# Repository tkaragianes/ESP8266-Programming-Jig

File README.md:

Repo to store design files, schematics, circuit layout, code, etc for an ESP8266 programming jig. Designed to service the ESP-01, ESP-12, & ESP-201 modules.

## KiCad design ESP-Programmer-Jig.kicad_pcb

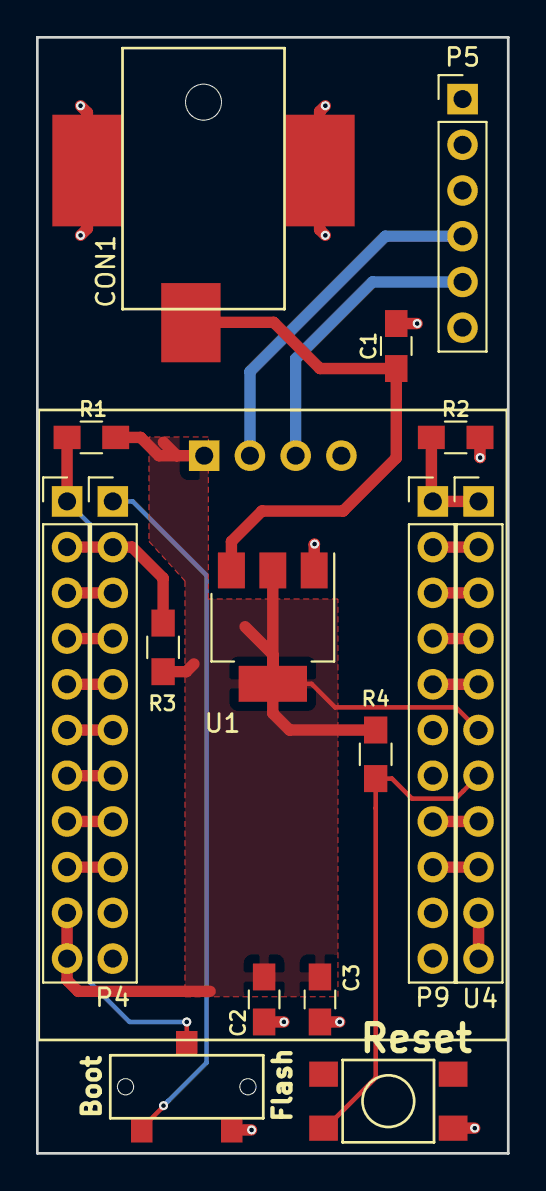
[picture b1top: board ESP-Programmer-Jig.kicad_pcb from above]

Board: 2 copper layers, 26.2 x 62.0 mm, 15 parts (0 on the bottom side), 23 nets.

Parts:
C1, C2: 10uF; C_0805_HandSoldering
C3: 0.1uF; C_0805_HandSoldering
CON1: BARREL_JACK; PJ-036AH-SMT_BarrelJack
P4, P9: CONN_01X11; Pin_Header_Straight_1x11_Pitch2.54mm
P5: CONN_01X06; Pin_Header_Straight_1x06_Pitch2.54mm
R1, R2, R3, R4: 10k; R_0805_HandSoldering
SW1: SW_PUSH; TL3305_Tact_Switch
SW2: SW_SPDT; Slide_Switch_SPDT
U1: AZ1117; SOT-223
U4: ESP-201; ESP-201_Socket

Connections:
+3V3: C2.1, C3.1, R1.1, R3.1, R4.1, U1.2, U1.4, U4.1, U4.14, U4.15, U4.21
CLK: P4.4, U4.8
CMD: P4.5, U4.9
D0: P4.6, U4.10
D1: P4.7, U4.11
D2: P4.3, U4.7
D3: P4.8, U4.12
Flash: R1.2, SW2.2, U4.5
GND: C1.2, C2.2, C3.2, CON1.2, CON1.3, P5.1, R2.1, SW1.2, SW2.3, U1.1, U4.4, U4.25, U4.26
IO0: P4.1, SW2.1
IO2: P4.2, R3.2, U4.6
IO4: P4.9, U4.13
IO5: P9.9, U4.24
IO12: P9.3, U4.18
IO13: P9.2, U4.17
IO14: P9.4, U4.19
IO15: P9.1, R2.2, U4.16
unnamed: C1.1, CON1.1, U1.3
Reset: R4.2, SW1.1, U4.22
RxD: P5.5, U4.3
T_Out: P9.8, U4.23
TxD: P5.4, U4.2
XPD: P9.5, U4.20

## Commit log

2017-07-30 Initial Commit - Add README
    Repo to track design of an ESP8266 programming jig.
2017-07-30 Add KiCAD project
    Create KiCAD project for circuit design and layout. Schematic finished
    (pending review).
2017-11-16 Snapshot: Rev A Produced
    The first version of this board was just sent out for production. This commit
    is to snapshot the state of the board at Rev A production.
